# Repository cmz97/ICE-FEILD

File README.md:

# ICE-FEILD
1.  iOS based iPhone Application that can communicate with a custom-made RF module with both text message and voice message via BLE protocol.
2.  Embedded System PCB design

# PCB Designs  #

##  Board ##

##  MCU ##

##  BLE ##

##  Buck Converter  ##

##  Two Cell li-po battery charger  ##

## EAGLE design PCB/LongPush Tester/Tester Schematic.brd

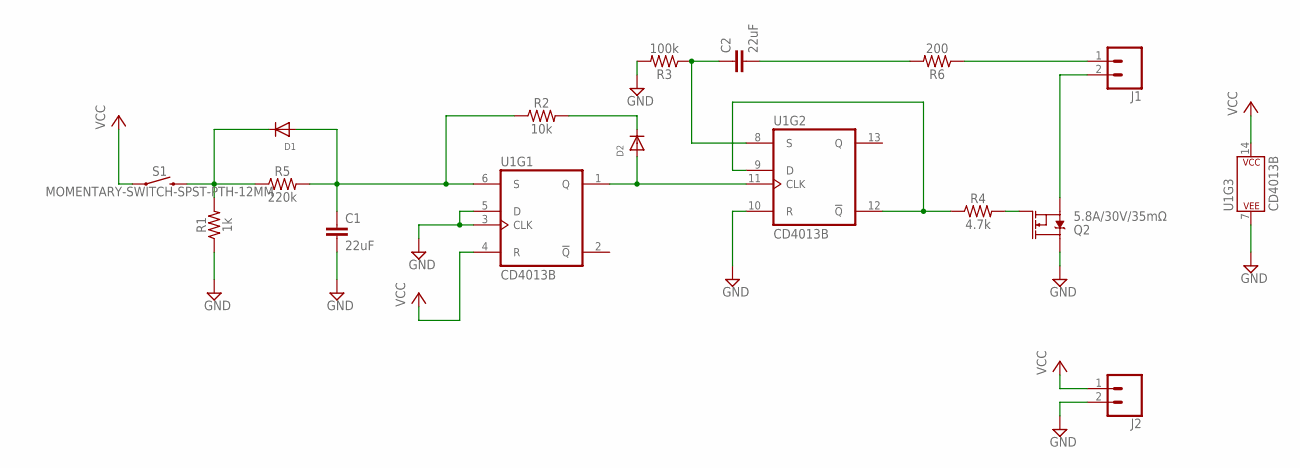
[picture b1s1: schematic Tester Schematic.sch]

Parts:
C1, C2: 22uF; 0805
D1, D2: DIODESOD-123; SOD-123
J1, J2: CONN_02; 1X02
Q2: 5.8A/30V/35mΩ; SOT23-3
R1: 1k; 0603
R2: 10k; 0603
R3: 100k; 0603
R4: 4.7k; 0603
R5: 220k; 0603
R6: 200; 0603
S1: MOMENTARY-SWITCH-SPST-PTH-12MM; TACTILE_SWITCH_PTH_12MM
U1: CD4013B; DIP14-KIT

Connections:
GND: C1.2, J2.2, Q2.3 (D), R1.1, R3.2, U1.3 (CLK), U1.5 (D), U1.7 (P$V-), U1.10 (R)
unnamed: C1.1, D1.A, R2.1, R5.2, U1.6 (S)
unnamed: D1.C, R1.2, R5.1, S1.3 (2)
unnamed: R4.1, U1.9 (D), U1.12 (!Q)
unnamed: D2.A, U1.1 (Q), U1.11 (CLK)
unnamed: D2.C, R2.2
unnamed: C2.1, R3.1, U1.8 (S)
unnamed: Q2.1 (G), R4.2
unnamed: J1.2, Q2.2 (S)
unnamed: C2.2, R6.2
unnamed: J1.1, R6.1
VCC: J2.1, S1.1, U1.4 (R), U1.14 (P$V+)

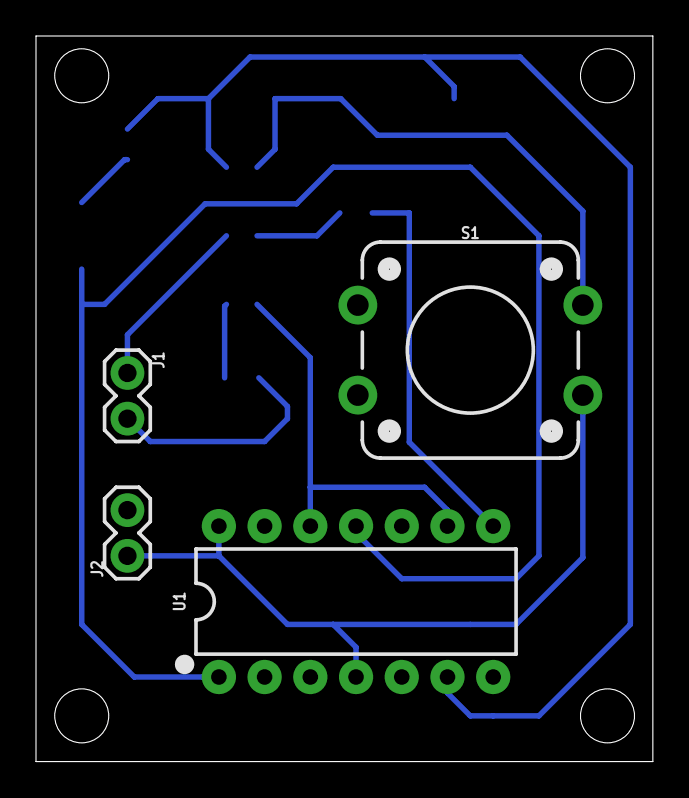
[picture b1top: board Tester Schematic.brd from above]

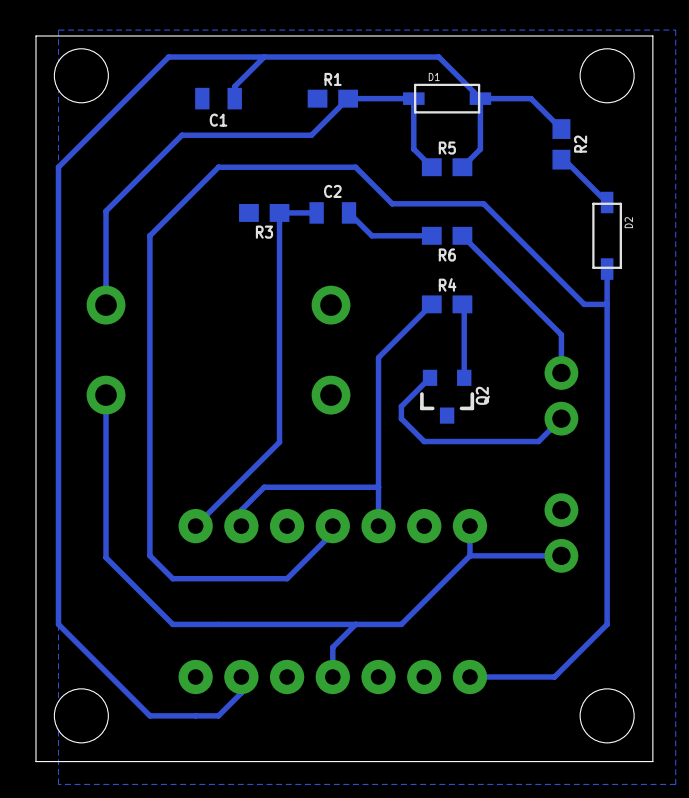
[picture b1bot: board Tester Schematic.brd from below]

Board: 2 copper layers, 34.3 x 40.3 mm, 15 parts (11 on the bottom side), 12 nets.

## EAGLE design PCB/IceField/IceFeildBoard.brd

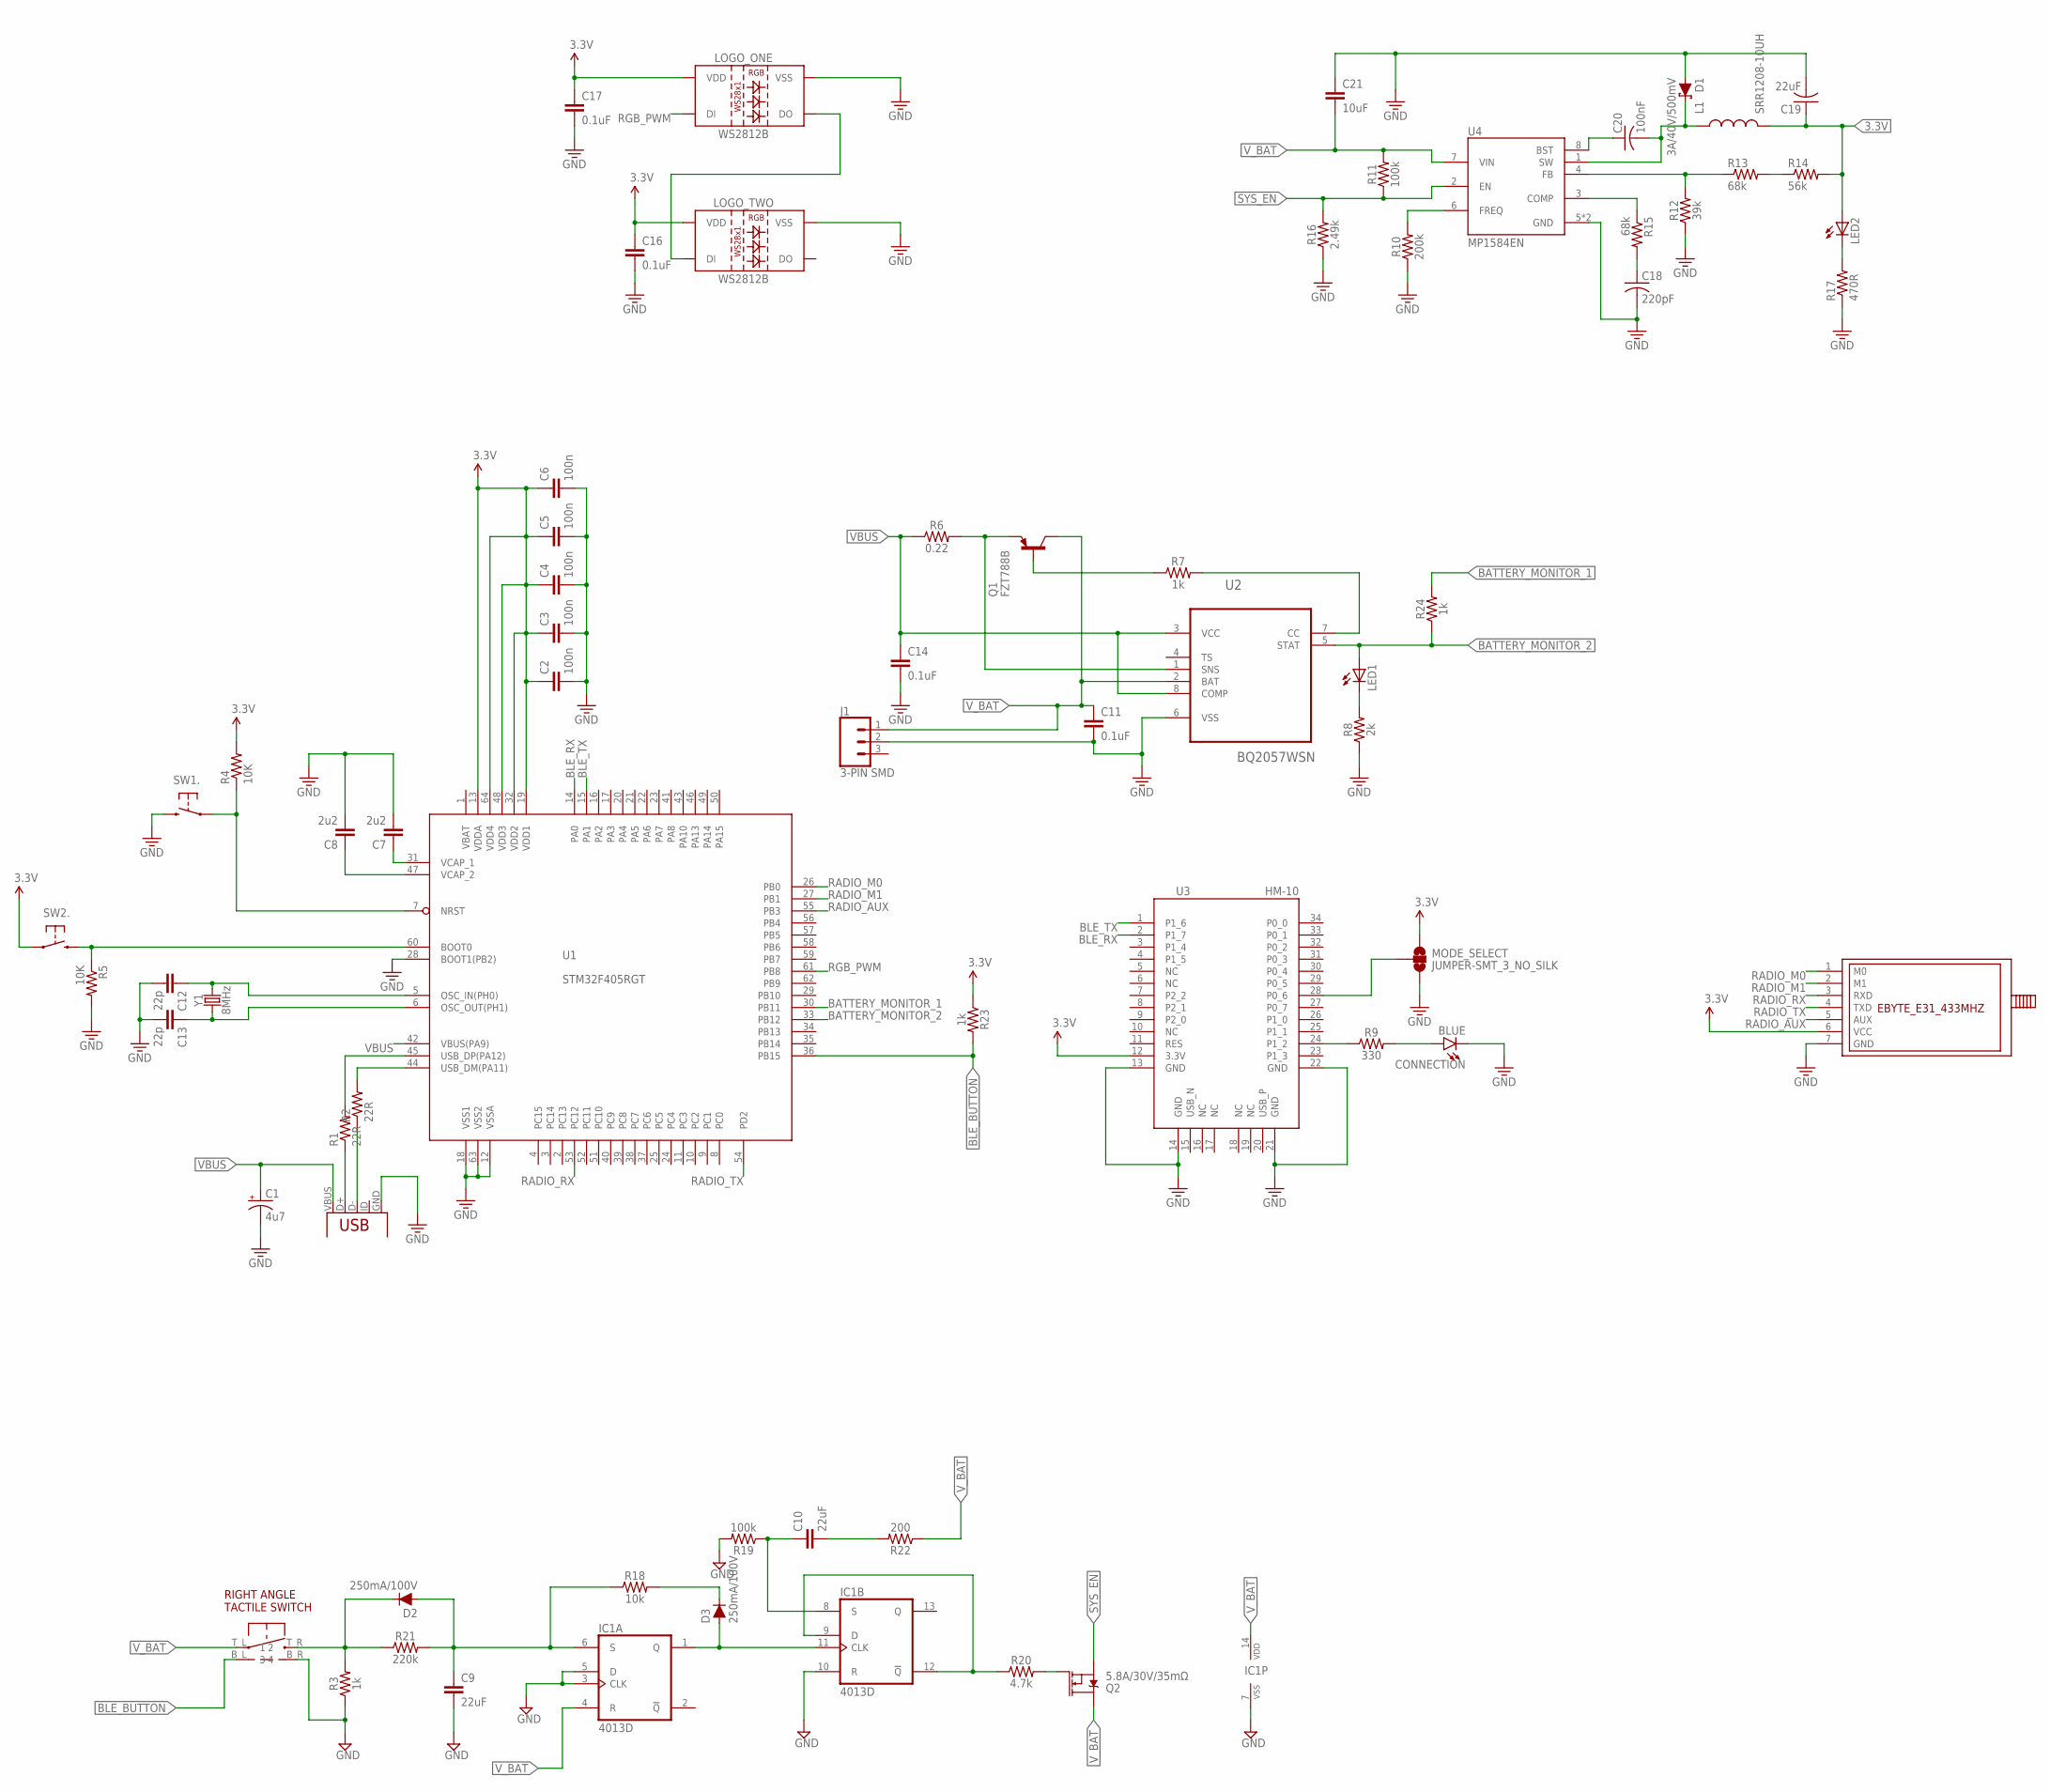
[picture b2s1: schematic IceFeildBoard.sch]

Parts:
C1: 4u7; EIA3216-KIT
C2, C3, C4, C5, C6: 100n; 0603-CAP
C7, C8: 2u2; 0603-CAP
C9, C10: 22uF; 0805
C11, C14, C16, C17: 0.1uF; 0603
C12, C13: 22p; 0603-CAP
C18: 220pF; C0603
C19: 22uF; C0603
C20: 100nF; C0603
C21: 10uF; 0603
CONNECTION: BLUE; LED-0603
D1: 3A/40V/500mV; SMA-DIODE
D2, D3: 250mA/100V; SOD-323
IC1: 4013D; SO14
J1: 3-PIN SMD; JST-3-SMD
L1: SRR1208-10UH; 1008
LED1, LED2: LED0603; LED-0603
LOGO_ONE: WS2812B
LOGO_TWO: WS2812B
MODE_SELECT: JUMPER-SMT_3_NO_SILK; SMT-JUMPER_3_NO_SILK
Q1: FZT788B; SOT230P700X180-4N
Q2: 5.8A/30V/35mΩ; SOT23-3
R1, R2: 22R; 0603-RES
R3, R7, R23, R24: 1k; 0603
R4, R5: 10K; 0603-RES
R6: 0.22; 0805
R8: 2k; 0603
R9: 330; 0603
R10: 200k; 0603
R11, R19: 100k; 0603
R12: 39k; 0603
R13, R15: 68k; R0603
R14: 56k; R0603
R16: 2.49k; 0603
R17: 470R; 0603-RES
R18: 10k; 0603
R20: 4.7k; 0603
R21: 220k; 0603
R22: 200; 0603
SW1: !RST; SWITCH-TACT-B3U-1100P-B
SW2: BOOT; SWITCH-TACT-B3U-1100P-B
U1: STM32F405RGT; LQFP64
U2: BQ2057WSN; SOIC127P600X175-8N
U3: HM-10
U4: MP1584EN; SOIC9P127_490X600X170L84X42T330X241N
U$1: RIGHT_ANGLE_TACTILE_SWITCH
U$2: EBYTE_E31_433MHZ
USB: USB-MICROB-SMD
Y1: 8MHz; CRYSTAL-SMD-5X3.2-4PAD

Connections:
3.3V: C2.1, C3.1, C4.1, C5.1, C6.1, C16.1, C17.1, C19.1, L1.2, LED2.A, LOGO_ONE.1 (VDD), LOGO_TWO.1 (VDD), MODE_SELECT.1, R4.2, R14.2, R23.1, SW2.1, U1.13 (VDDA), U1.19 (VDD1), U1.32 (VDD2), U1.48 (VDD3), U1.64 (VDD4), U3.12 (3.3V), U$2.6 (VCC)
BATTERY_MONITOR_1: R24.2, U1.30 (PB11)
BATTERY_MONITOR_2: LED1.A, R24.1, U1.33 (PB12), U2.5 (STAT)
BLE_BUTTON: R23.2, U1.36 (PB15), U$1.B_L (3)
BLE_RX: U1.14 (PA0), U3.2 (P1_7)
BLE_TX: U1.15 (PA1), U3.1 (P1_6)
GND: C1.C (-), C2.2, C3.2, C4.2, C5.2, C6.2, C7.2, C8.2, C9.2, C11.2, C12.2, C13.2, C14.2, C16.2, C17.2, C18.2, C19.2, C21.1, CONNECTION.C, D1.A, IC1.3 (CLK), IC1.5 (D), IC1.7 (VSS), IC1.10 (R), J1.2, LOGO_ONE.3 (VSS), LOGO_TWO.3 (VSS), MODE_SELECT.3, R3.1, R5.2, R8.1, R10.1, R12.1, R16.1, R17.1, R19.2, SW1.2, U1.12 (VSSA), U1.18 (VSS1), U1.28 (BOOT1(PB2)), U1.63 (VSS2), U2.6 (VSS), U3.13 (GND), U3.14 (GND), U3.21 (GND), U3.22 (GND), U4.5 (GND), U4.9 (GND), U$1.B_R (4), U$2.7 (GND), USB.GND
unnamed: R1.2, U1.45 (USB_DP(PA12))
unnamed: R2.2, U1.44 (USB_DM(PA11))
unnamed: C14.1, R6.1, U2.3 (VCC), U2.8 (COMP)
unnamed: R1.1, USB.D+
unnamed: R2.1, USB.D-
unnamed: CONNECTION.A, R9.2
unnamed: C9.1, D2.A, IC1.6 (S), R18.1, R21.2
unnamed: R9.1, U3.24 (P1_2)
unnamed: MODE_SELECT.2, U3.28 (P0_6)
unnamed: LOGO_ONE.2 (DO), LOGO_TWO.4 (DI)
unnamed: C13.1, U1.6 (OSC_OUT(PH1)), Y1.1
unnamed: C7.1, U1.31 (VCAP_1)
unnamed: C8.1, U1.47 (VCAP_2)
unnamed: C12.1, U1.5 (OSC_IN(PH0)), Y1.3 (2)
unnamed: R5.1, SW2.2, U1.60 (BOOT0)
unnamed: R4.1, SW1.1, U1.7 (NRST)
unnamed: Q1.3 (E), R6.2, U2.1 (SNS)
unnamed: Q1.1 (B), R7.1
unnamed: R13.2, R14.1
unnamed: D2.C, R3.2, R21.1, U$1.T_R (2)
unnamed: R12.2, R13.1, U4.4 (FB)
unnamed: C20.2, D1.C, L1.1, U4.1 (SW)
unnamed: C20.1, U4.8 (BST)
unnamed: LED2.C, R17.2
unnamed: D3.A, IC1.1 (Q), IC1.11 (CLK)
unnamed: D3.C, R18.2
unnamed: R15.1, U4.3 (COMP)
unnamed: C18.1, R15.2
unnamed: IC1.9 (D), IC1.12 (!Q), R20.1
unnamed: C10.1, IC1.8 (S), R19.1
unnamed: R10.2, U4.6 (FREQ)
unnamed: Q2.1 (G), R20.2
unnamed: R7.2, U2.7 (CC)
unnamed: C10.2, R22.2
unnamed: LED1.C, R8.2
RADIO_AUX: U1.55 (PB3), U$2.5 (AUX)
RADIO_M0: U1.26 (PB0), U$2.1 (M0)
RADIO_M1: U1.27 (PB1), U$2.2 (M1)
RADIO_RX: U1.53 (PC12), U$2.3 (RXD)
RADIO_TX: U1.54 (PD2), U$2.4 (TXD)
RGB_PWM: LOGO_ONE.4 (DI), U1.61 (PB8)
SYS_EN: Q2.2 (S), R11.1, R16.2, U4.2 (EN)
VBAT: U1.1 (VBAT)
VBUS: C1.A (+), U1.42 (VBUS(PA9)), USB.VBUS
V_BAT: C11.1, C21.2, IC1.4 (R), IC1.14 (VDD), J1.1 (3), Q1.2 (C), Q1.4 (C), Q2.3 (D), R11.2, R22.1, U2.2 (BAT), U4.7 (VIN), U$1.T_L (1)

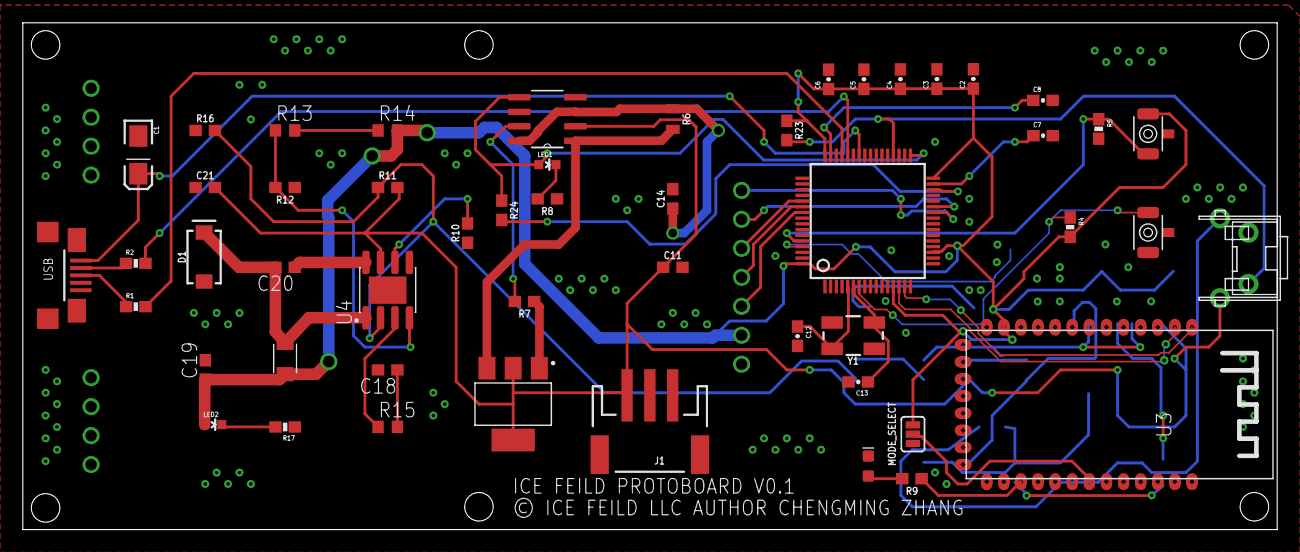
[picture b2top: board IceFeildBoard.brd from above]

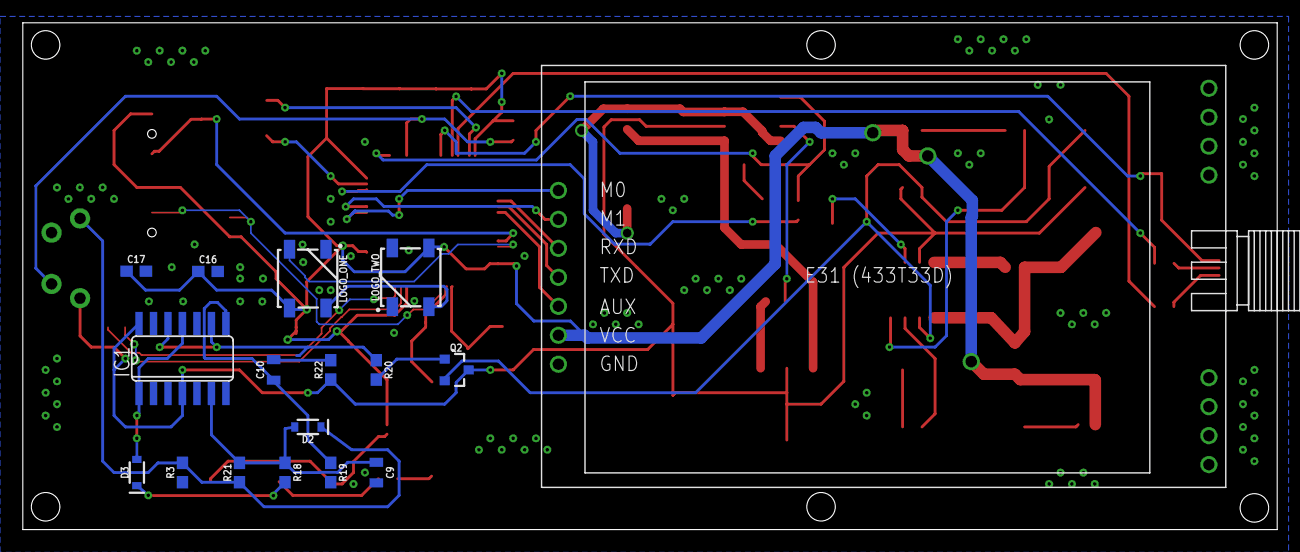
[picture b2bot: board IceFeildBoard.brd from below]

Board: 2 copper layers, 110.0 x 44.4 mm, 68 parts (17 on the bottom side), 51 nets.

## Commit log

2018-10-21 Project ICE FEILD
2018-11-03 add image

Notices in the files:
PCB/IceField/IceFeildBoard.brd:
© ICE FEILD LLC AUTHOR CHENGMING ZHANG
parts and their libraries:
SparkFun-Capacitors: Licensing: Creative Commons ShareAlike 4.0 International - https://creativecommons.org/licenses/by-sa/4.0
